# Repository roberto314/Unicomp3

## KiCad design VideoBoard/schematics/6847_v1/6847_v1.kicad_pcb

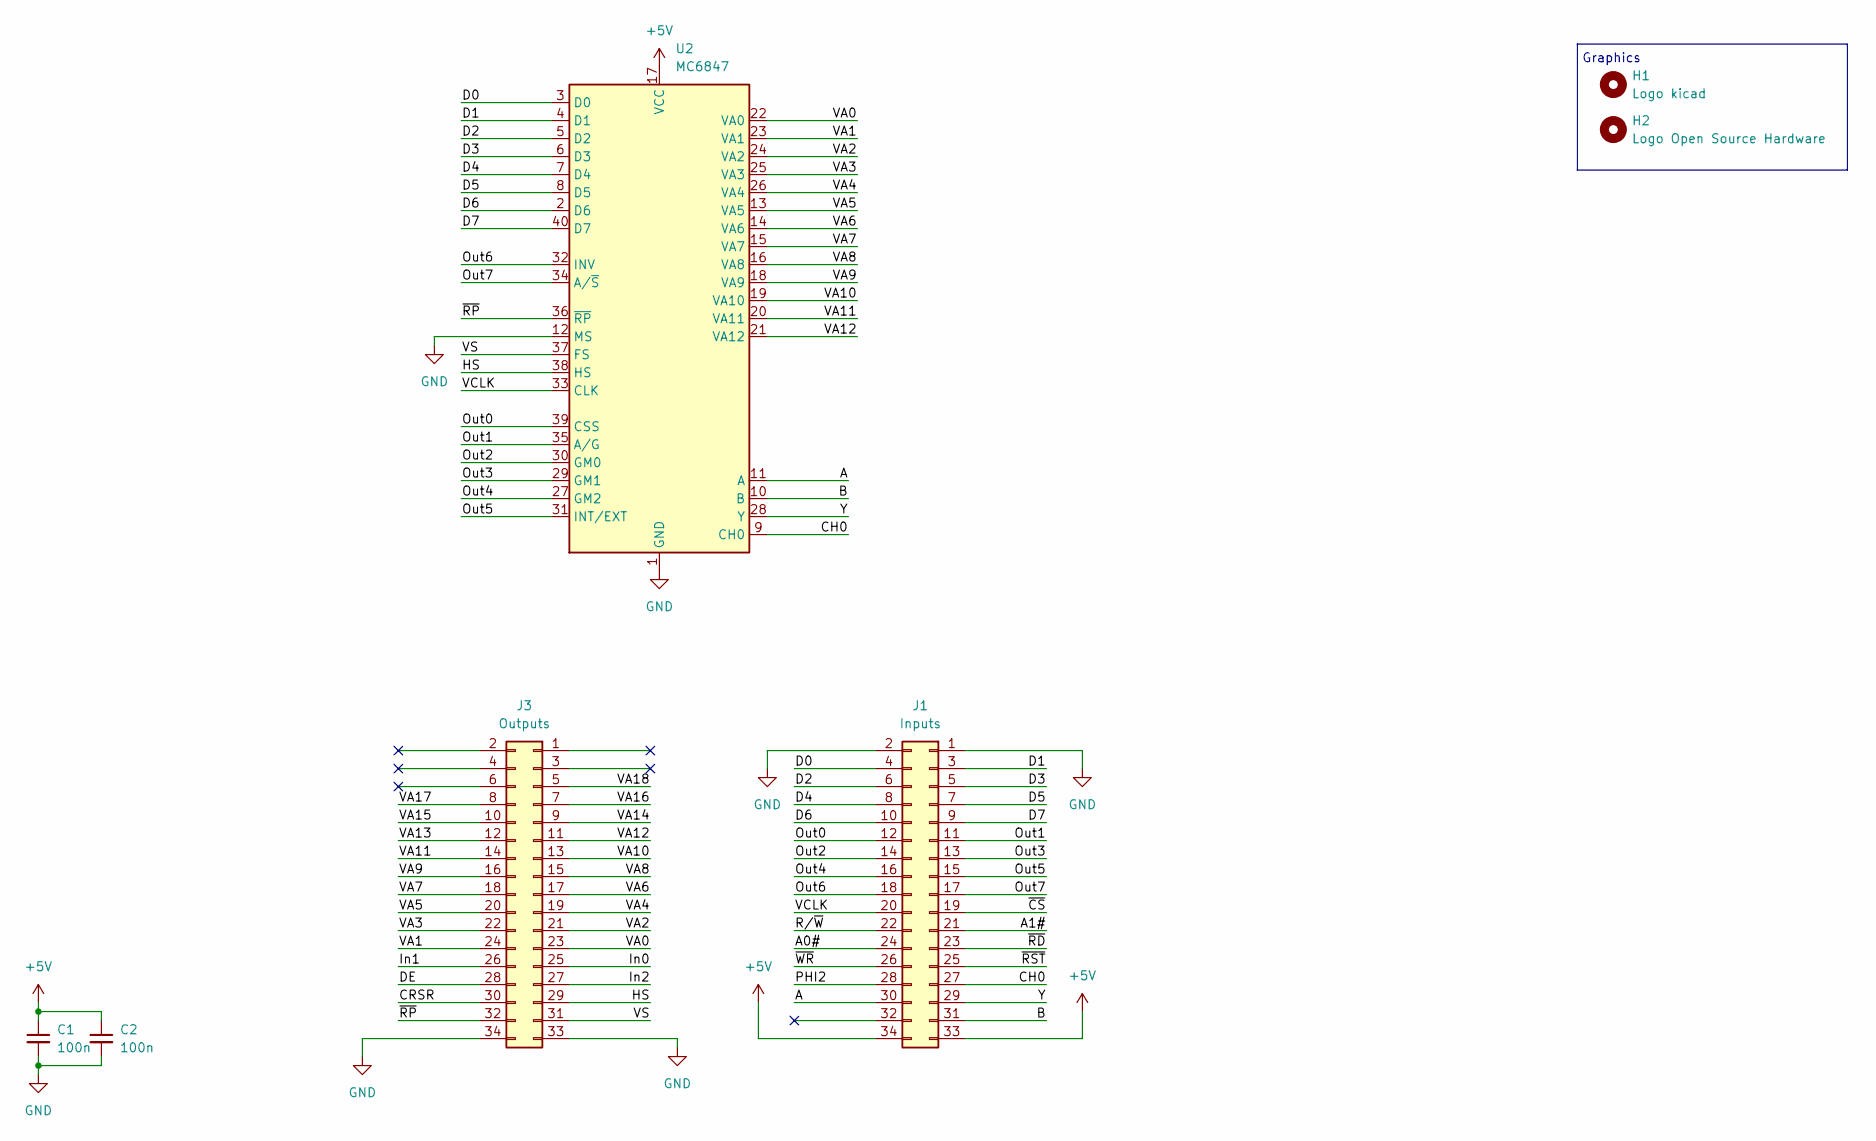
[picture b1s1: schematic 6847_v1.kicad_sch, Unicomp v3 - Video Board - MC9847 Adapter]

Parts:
C1, C2: 100n; C_1206_3216Metric_Pad1.33x1.80mm_HandSolder
H1: Logo kicad; KiCad-Logo2_6mm_SilkScreen
H2: Logo Open Source Hardware; OSHW-Logo2_7.3x6mm_SilkScreen
J1: Inputs; PinHeader_2x17_P2.54mm_Vertical
J3: Outputs; PinHeader_2x17_P2.54mm_Vertical
U2: MC6847; DIP-40_W15.24mm

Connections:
+5V: C1.1, C2.1, J1.33, J1.34, U2.17 (VCC)
/A: J1.30, U2.11 (A)
/A0#: J1.24
/A1#: J1.21
/B: J1.31, U2.10 (B)
/CH0: J1.27, U2.9 (CH0)
/CRSR: J3.30
/D0: J1.4, U2.3 (D0)
/D1: J1.3, U2.4 (D1)
/D2: J1.6, U2.5 (D2)
/D3: J1.5, U2.6 (D3)
/D4: J1.8, U2.7 (D4)
/D5: J1.7, U2.8 (D5)
/D6: J1.10, U2.2 (D6)
/D7: J1.9, U2.40 (D7)
/DE: J3.28
/HS: J3.29, U2.38 (HS)
/In0: J3.25
/In1: J3.26
/In2: J3.27
/Out0: J1.12, U2.39 (CSS)
/Out1: J1.11, U2.35 (A/G)
/Out2: J1.14, U2.30 (GM0)
/Out3: J1.13, U2.29 (GM1)
/Out4: J1.16, U2.27 (GM2)
/Out5: J1.15, U2.31 (INT/EXT)
/Out6: J1.18, U2.32 (INV)
/Out7: J1.17, U2.34 (A/~S)
/PHI2: J1.28
/R/~W: J1.22
/VA0: J3.23, U2.22 (VA0)
/VA1: J3.24, U2.23 (VA1)
/VA2: J3.21, U2.24 (VA2)
/VA3: J3.22, U2.25 (VA3)
/VA4: J3.19, U2.26 (VA4)
/VA5: J3.20, U2.13 (VA5)
/VA6: J3.17, U2.14 (VA6)
/VA7: J3.18, U2.15 (VA7)
/VA8: J3.15, U2.16 (VA8)
/VA9: J3.16, U2.18 (VA9)
/VA10: J3.13, U2.19 (VA10)
/VA11: J3.14, U2.20 (VA11)
/VA12: J3.11, U2.21 (VA12)
/VA13: J3.12
/VA14: J3.9
/VA15: J3.10
/VA16: J3.7
/VA17: J3.8
/VA18: J3.5
/VCLK: J1.20, U2.33 (CLK)
/VS: J3.31, U2.37 (FS)
/Y: J1.29, U2.28 (Y)
/~CS: J1.19
/~RD: J1.23
/~RP: J3.32, U2.36 (~RP)
/~RST: J1.25
/~WR: J1.26
GND: C1.2, C2.2, J1.1, J1.2, J3.33, J3.34, U2.1 (GND), U2.12 (MS)

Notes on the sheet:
Graphics

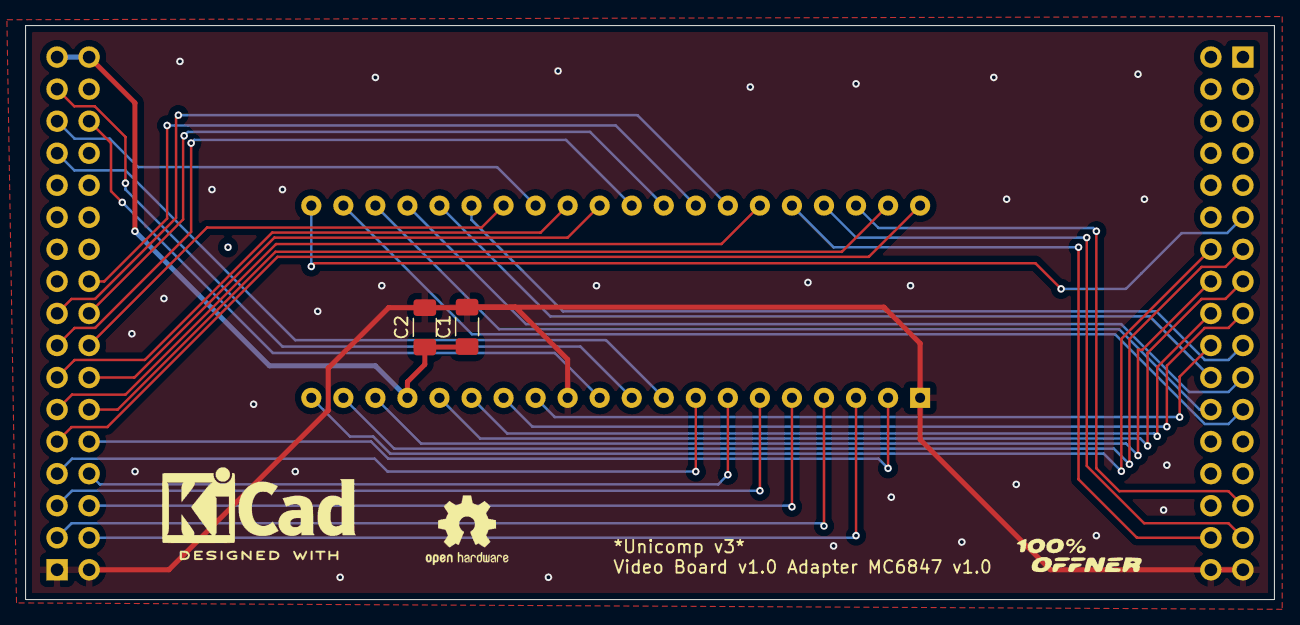
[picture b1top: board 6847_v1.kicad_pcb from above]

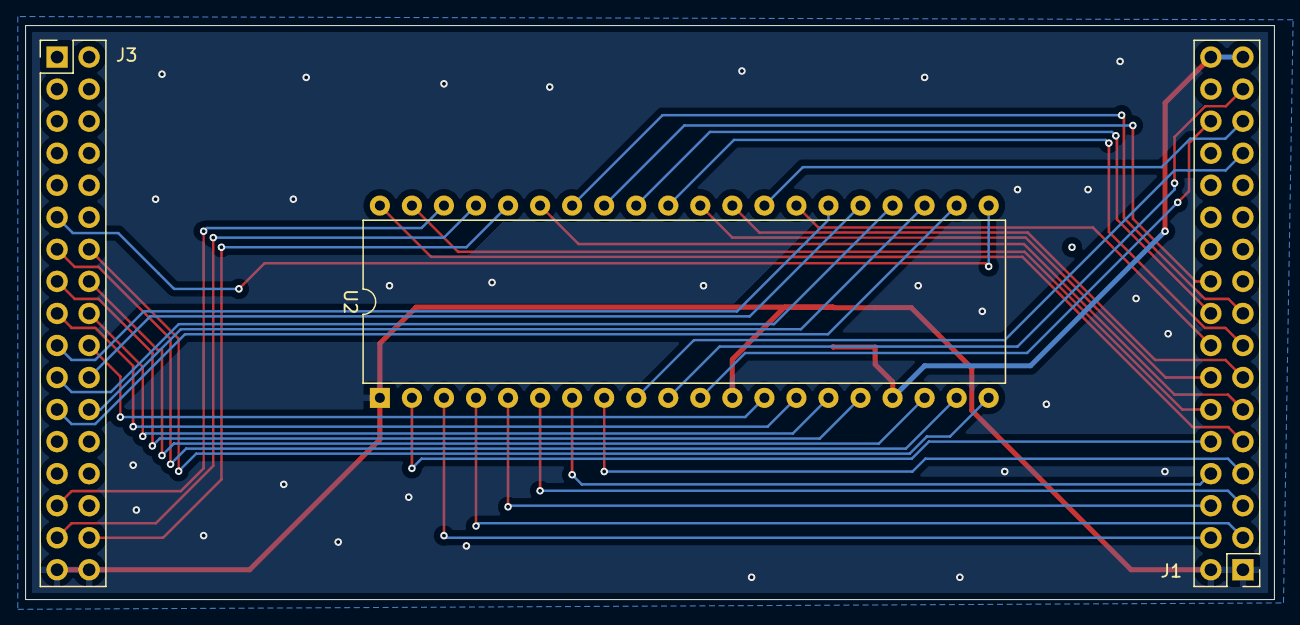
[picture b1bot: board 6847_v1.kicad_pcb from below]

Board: 2 copper layers, 99.0 x 45.5 mm, 7 parts (3 on the bottom side), 39 nets.

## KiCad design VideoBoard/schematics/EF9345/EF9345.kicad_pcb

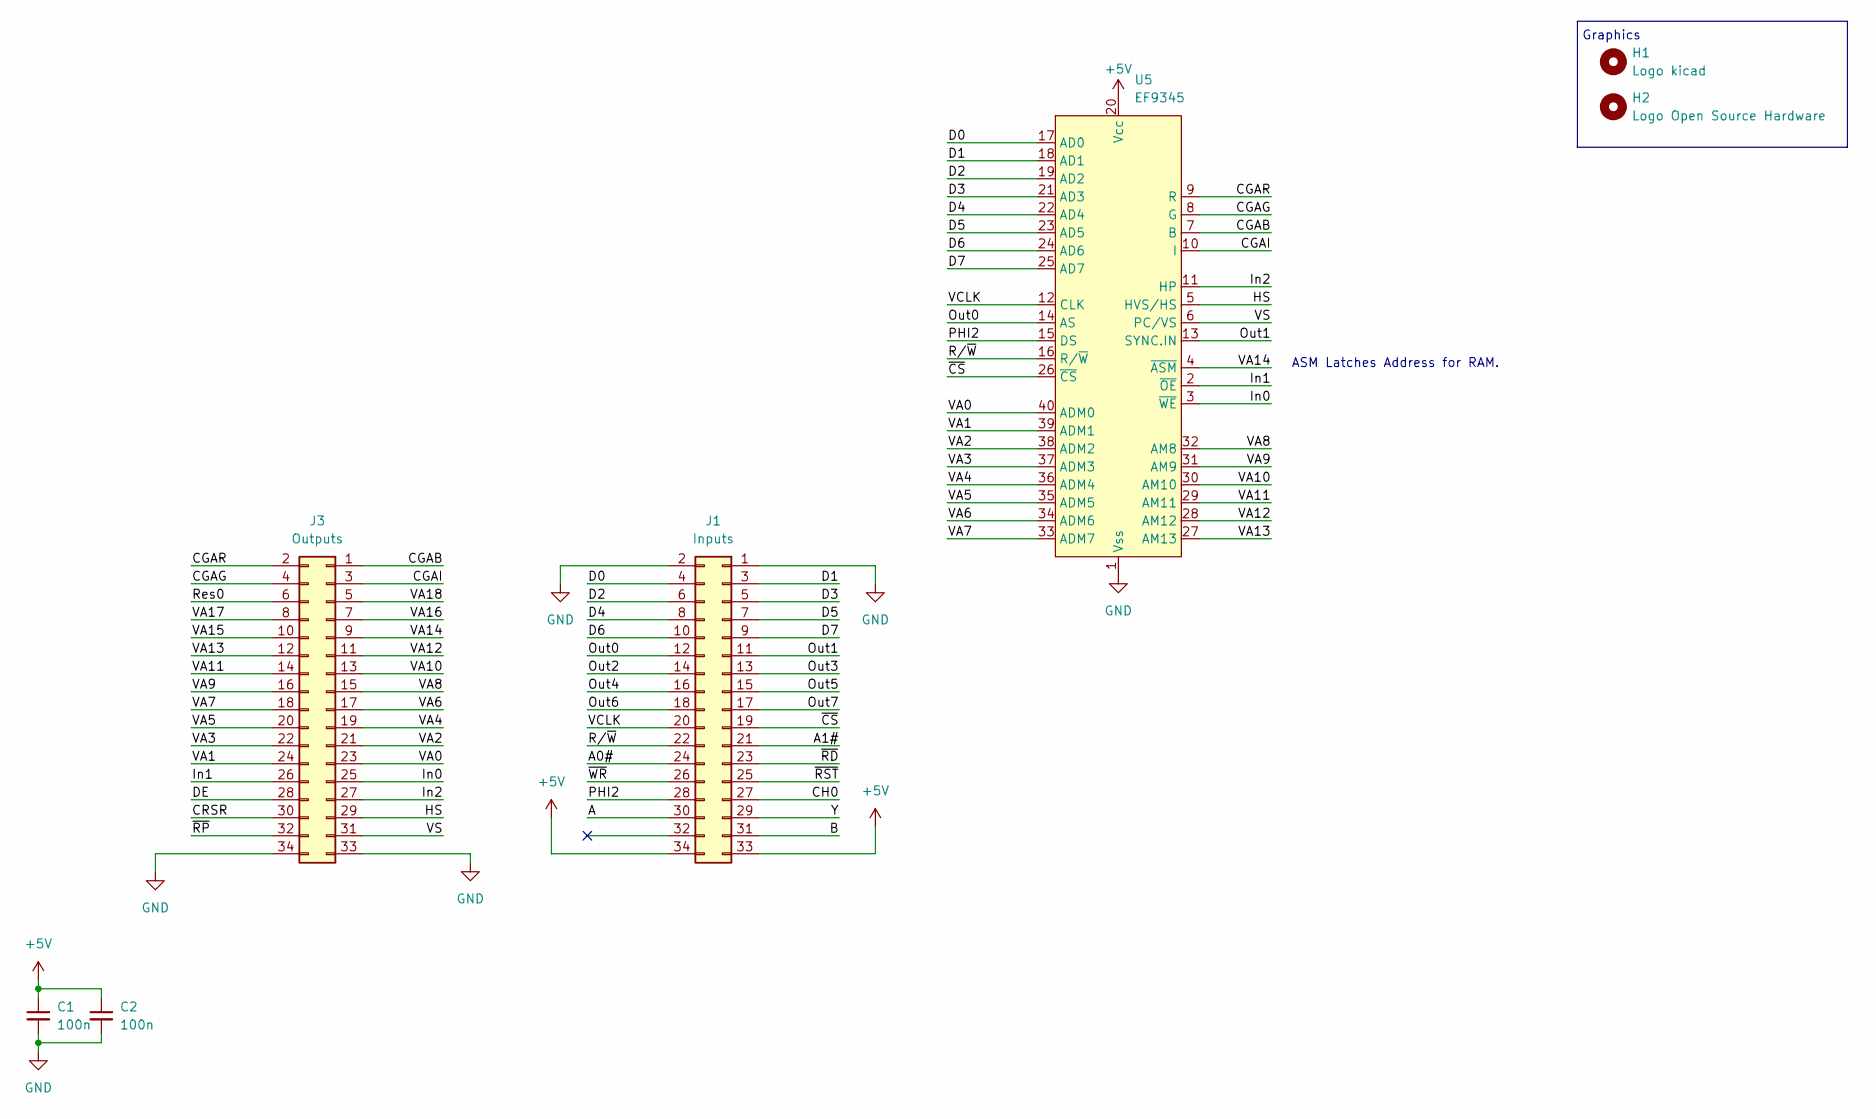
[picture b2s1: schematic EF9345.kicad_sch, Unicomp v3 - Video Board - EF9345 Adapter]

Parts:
C1, C2: 100n; C_1206_3216Metric_Pad1.33x1.80mm_HandSolder
H1: Logo kicad; KiCad-Logo2_6mm_SilkScreen
H2: Logo Open Source Hardware; OSHW-Logo2_7.3x6mm_SilkScreen
J1: Inputs; PinHeader_2x17_P2.54mm_Vertical
J3: Outputs; PinHeader_2x17_P2.54mm_Vertical
U5: EF9345; DIP-40_W15.24mm_Socket

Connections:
+5V: C1.1, C2.1, J1.33, J1.34, U5.20 (Vcc)
/A: J1.30
/A0#: J1.24
/A1#: J1.21
/B: J1.31
/CGAB: J3.1, U5.7 (B)
/CGAG: J3.4, U5.8 (G)
/CGAI: J3.3, U5.10 (I)
/CGAR: J3.2, U5.9 (R)
/CH0: J1.27
/CRSR: J3.30
/D0: J1.4, U5.17 (AD0)
/D1: J1.3, U5.18 (AD1)
/D2: J1.6, U5.19 (AD2)
/D3: J1.5, U5.21 (AD3)
/D4: J1.8, U5.22 (AD4)
/D5: J1.7, U5.23 (AD5)
/D6: J1.10, U5.24 (AD6)
/D7: J1.9, U5.25 (AD7)
/DE: J3.28
/HS: J3.29, U5.5 (HVS/HS)
/In0: J3.25, U5.3 (~WE)
/In1: J3.26, U5.2 (~OE)
/In2: J3.27, U5.11 (HP)
/Out0: J1.12, U5.14 (AS)
/Out1: J1.11, U5.13 (SYNC.IN)
/Out2: J1.14
/Out3: J1.13
/Out4: J1.16
/Out5: J1.15
/Out6: J1.18
/Out7: J1.17
/PHI2: J1.28, U5.15 (DS)
/Res0: J3.6
/R/~W: J1.22, U5.16 (R/~W)
/VA0: J3.23, U5.40 (ADM0)
/VA1: J3.24, U5.39 (ADM1)
/VA2: J3.21, U5.38 (ADM2)
/VA3: J3.22, U5.37 (ADM3)
/VA4: J3.19, U5.36 (ADM4)
/VA5: J3.20, U5.35 (ADM5)
/VA6: J3.17, U5.34 (ADM6)
/VA7: J3.18, U5.33 (ADM7)
/VA8: J3.15, U5.32 (AM8)
/VA9: J3.16, U5.31 (AM9)
/VA10: J3.13, U5.30 (AM10)
/VA11: J3.14, U5.29 (AM11)
/VA12: J3.11, U5.28 (AM12)
/VA13: J3.12, U5.27 (AM13)
/VA14: J3.9, U5.4 (~ASM)
/VA15: J3.10
/VA16: J3.7
/VA17: J3.8
/VA18: J3.5
/VCLK: J1.20, U5.12 (CLK)
/VS: J3.31, U5.6 (PC/VS)
/Y: J1.29
/~CS: J1.19, U5.26 (~CS)
/~RD: J1.23
/~RP: J3.32
/~RST: J1.25
/~WR: J1.26
GND: C1.2, C2.2, J1.1, J1.2, J3.33, J3.34, U5.1 (Vss)

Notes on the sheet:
Graphics
ASM Latches Address for RAM.

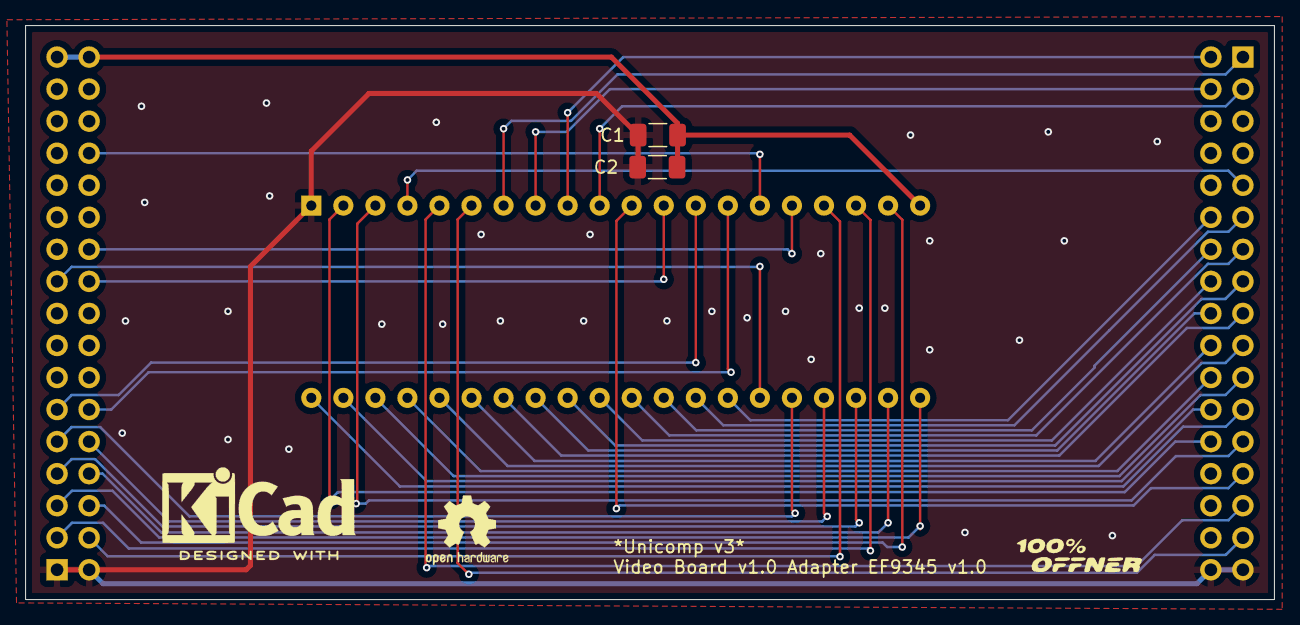
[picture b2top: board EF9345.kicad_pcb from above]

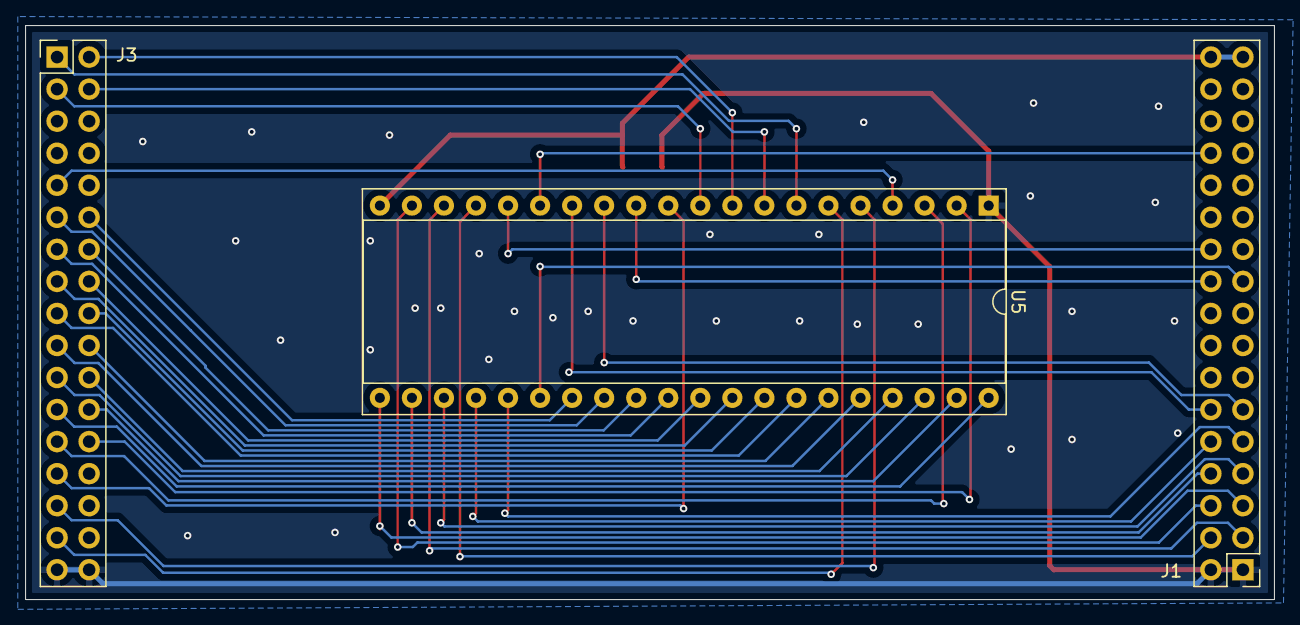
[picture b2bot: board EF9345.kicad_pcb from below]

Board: 2 copper layers, 99.0 x 45.5 mm, 7 parts (3 on the bottom side), 40 nets.

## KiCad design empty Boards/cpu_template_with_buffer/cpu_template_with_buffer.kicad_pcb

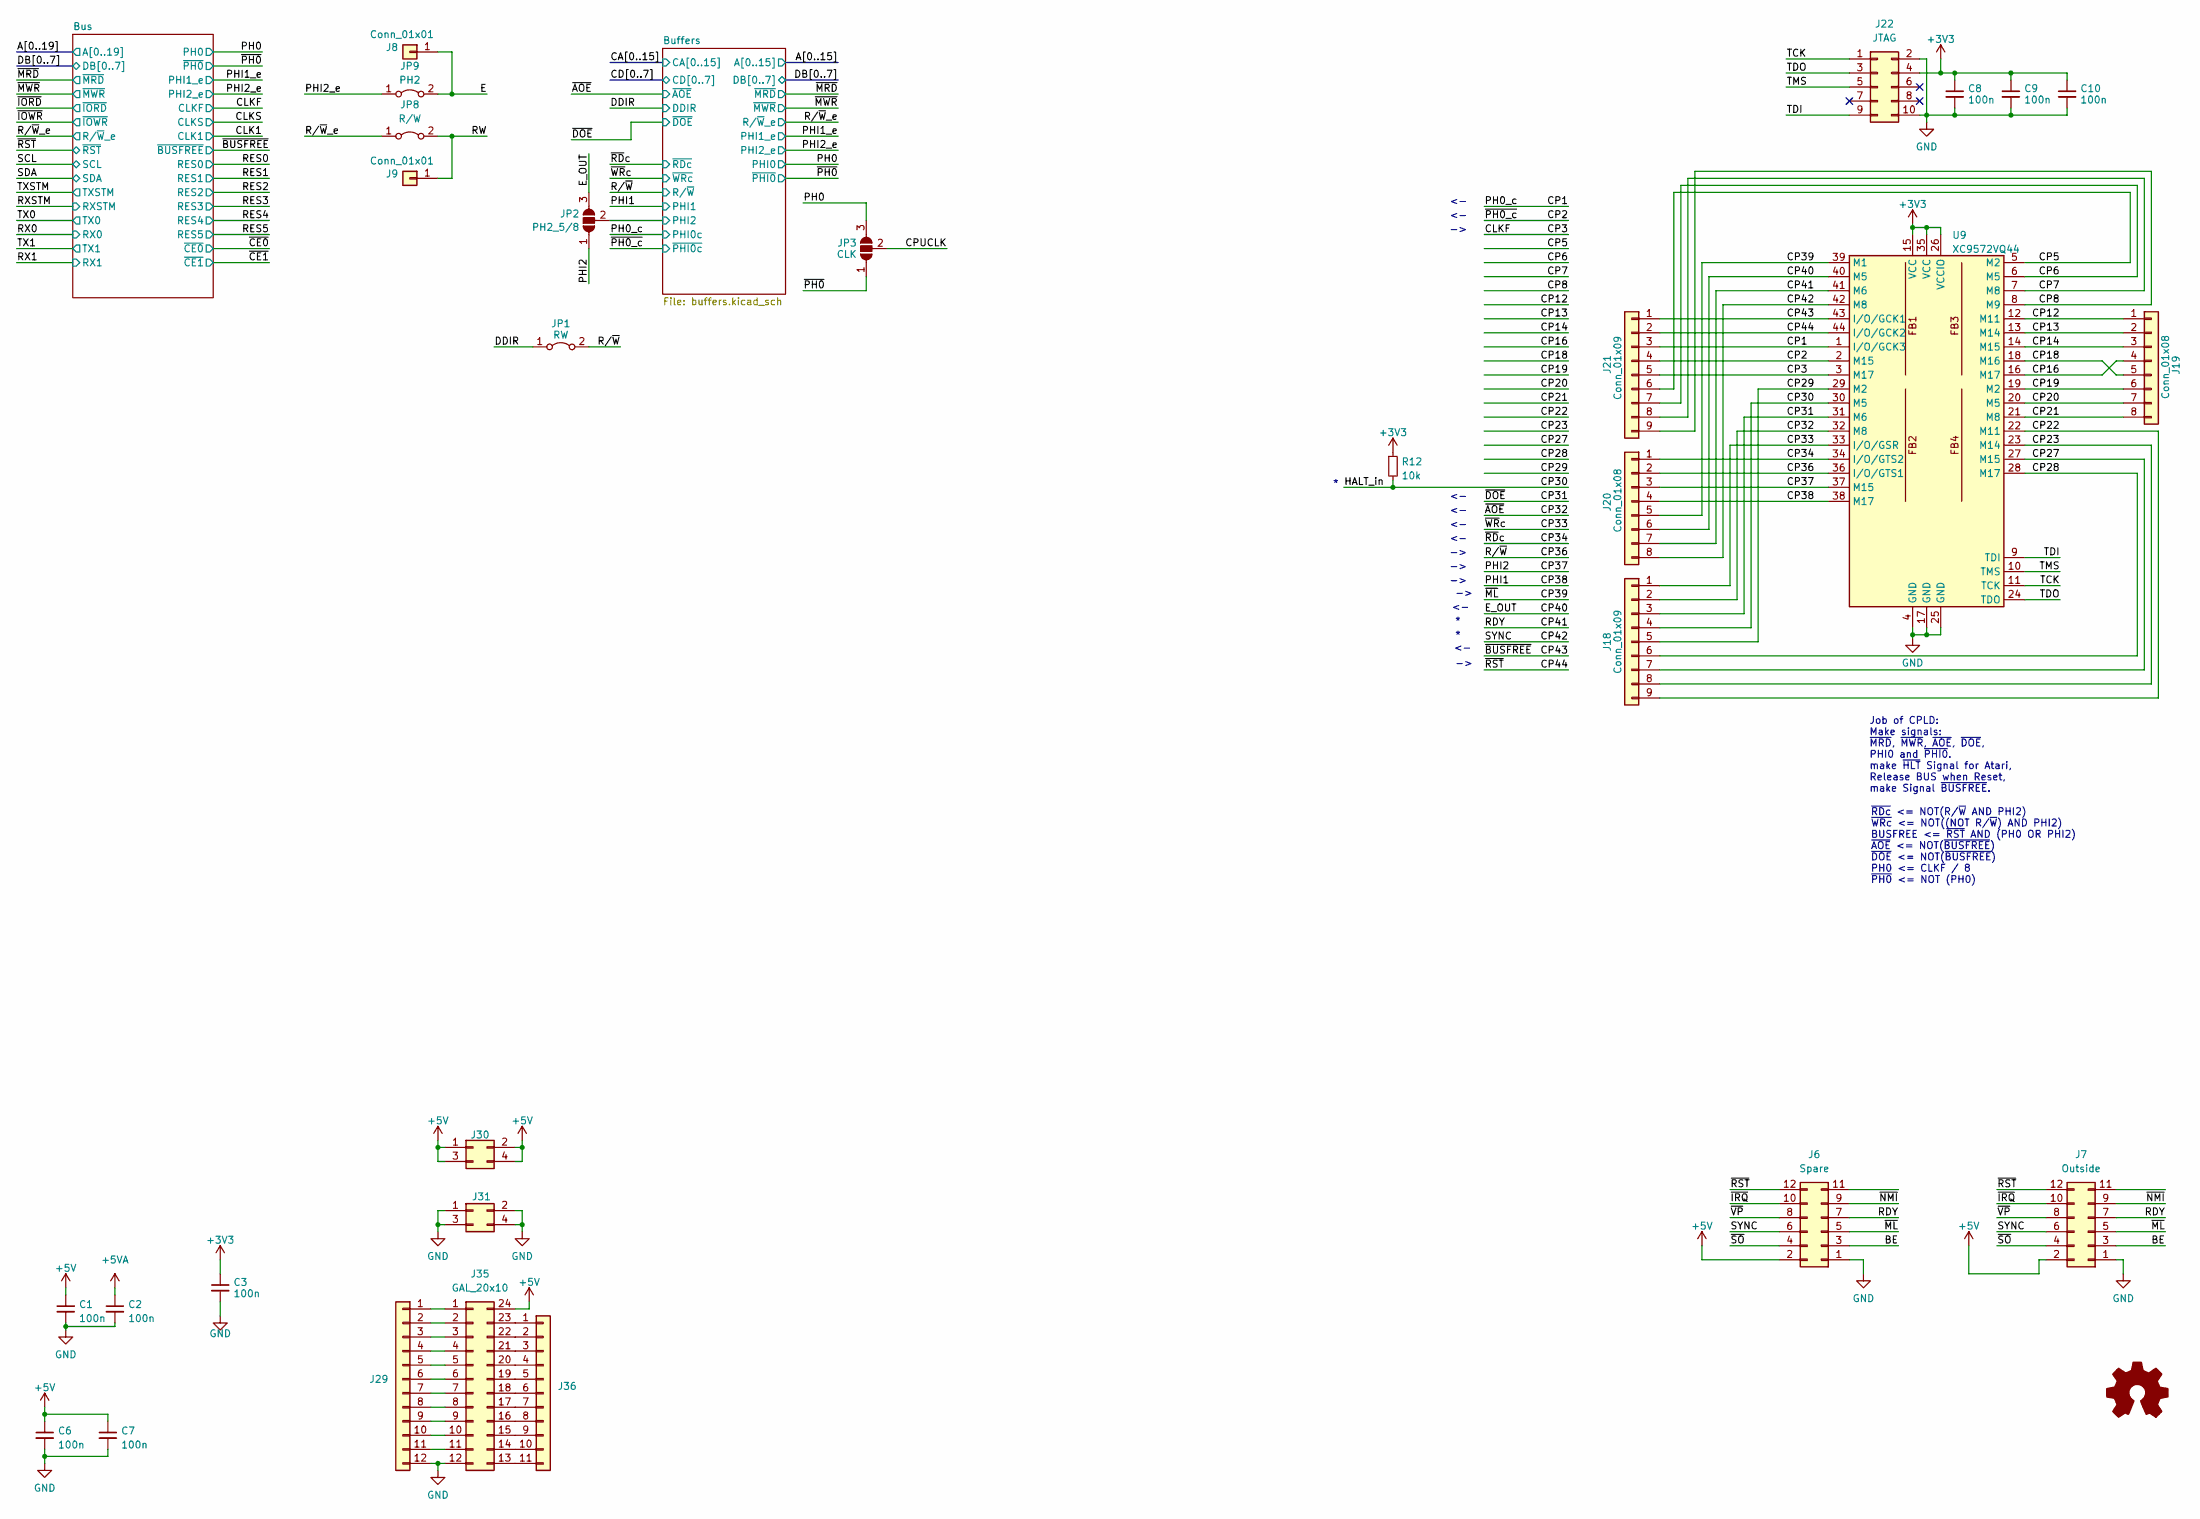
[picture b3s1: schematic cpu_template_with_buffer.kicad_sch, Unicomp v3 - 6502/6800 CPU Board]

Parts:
C1, C2, C3, C6, C7, C8, C9, C10: 100n; C_1206_3216Metric
J6: Spare; PinHeader_2x06_P2.54mm_Vertical
J7: Outside; PinHeader_2x06_P2.54mm_Horizontal
J8, J9: Conn_01x01; PinHeader_1x01_P2.00mm_Vertical
J18, J21: Conn_01x09; PinHeader_1x09_P2.54mm_Vertical
J19, J20: Conn_01x08; PinHeader_1x08_P2.54mm_Vertical
J22: JTAG; PinHeader_2x05_P2.54mm_Horizontal
J29: Conn_01x12; PinSocket_1x12_P2.54mm_Vertical
J30, J31: Conn_02x02_Odd_Even; PinSocket_2x02_P2.54mm_Vertical
J35: GAL_20x10; DIP-24_W7.62mm
J36: Conn_01x11; PinSocket_1x11_P2.54mm_Vertical
JP1: RW; SolderJumper-2_P1.3mm_Bridged_RoundedPad1.0x1.5mm
JP2: PH2_5/8; SolderJumper-3_P1.3mm_Open_RoundedPad1.0x1.5mm_NumberLabels
JP3: CLK; SolderJumper-3_P1.3mm_Open_RoundedPad1.0x1.5mm_NumberLabels
JP8: R/W; SolderJumper-2_P1.3mm_Bridged_RoundedPad1.0x1.5mm
JP9: PH2; SolderJumper-2_P1.3mm_Bridged_RoundedPad1.0x1.5mm
R12: 10k; R_1206_3216Metric_Pad1.30x1.75mm_HandSolder
U9: XC9572VQ44; TQFP-44_10x10mm_P0.8mm

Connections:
+3V3: C3.1, C8.1, C9.1, C10.1, J22.4, R12.1, U9.15 (VCC), U9.26 (VCCIO), U9.35 (VCC); also elsewhere on the board
+5V: C1.1, C6.1, C7.1, J6.2, J7.2, J30.1, J30.2, J30.3, J30.4, J35.24; also elsewhere on the board
+5VA: C2.1; also elsewhere on the board
/BE: J6.3, J7.3
/Buffers/PHI2: JP2.2 (C); also elsewhere on the board
/CLKF: J21.5, U9.3 (M17); also elsewhere on the board
/CP1: J21.3, U9.1 (I/O/GCK3); also elsewhere on the board
/CP2: J21.4, U9.2 (M15); also elsewhere on the board
/CP5: J21.6, U9.5 (M2)
/CP6: J21.7, U9.6 (M5)
/CP7: J21.8, U9.7 (M8)
/CP8: J21.9, U9.8 (M9)
/CP12: J19.1, U9.12 (M11)
/CP13: J19.2, U9.13 (M14)
/CP14: J19.3, U9.14 (M15)
/CP16: J19.4, U9.16 (M17)
/CP18: J19.5, U9.18 (M16)
/CP19: J19.6, U9.19 (M2)
/CP20: J19.7, U9.20 (M5)
/CP21: J19.8, U9.21 (M8)
/CP22: J18.9, U9.22 (M11)
/CP23: J18.8, U9.23 (M14)
/CP27: J18.7, U9.27 (M15)
/CP28: J18.6, U9.28 (M17)
/CP29: J18.5, U9.29 (M2)
/CP30: J18.4, R12.2, U9.30 (M5)
/CP31: J18.3, U9.31 (M6); also elsewhere on the board
/CP32: J18.2, U9.32 (M8); also elsewhere on the board
/CP33: J18.1, U9.33 (I/O/GSR); also elsewhere on the board
/CP34: J20.1, U9.34 (I/O/GTS2); also elsewhere on the board
/CP36: J20.2, JP1.2 (B), U9.36 (I/O/GTS1); also elsewhere on the board
/CP37: J20.3, JP2.1 (A), U9.37 (M15)
/CP38: J20.4, U9.38 (M17); also elsewhere on the board
/CP39: J6.5, J7.5, J20.5, U9.39 (M1)
/CP40: J20.6, JP2.3 (B), U9.40 (M5)
/CP41: J6.7, J7.7, J20.7, U9.41 (M6)
/CP42: J6.6, J7.6, J20.8, U9.42 (M8)
/CP43: J21.1, U9.43 (I/O/GCK1); also elsewhere on the board
/CP44: J6.12, J7.12, J21.2, U9.44 (I/O/GCK2); also elsewhere on the board
/CPUCLK: JP3.2 (C)
/DDIR: JP1.1 (A); also elsewhere on the board
/E: J8.1, JP9.2 (B)
/PH0: JP3.3 (B); also elsewhere on the board
/PHI2_e: JP9.1 (A); also elsewhere on the board
/RW: J9.1, JP8.2 (B)
/R/~W_e: JP8.1 (A); also elsewhere on the board
/TCK: J22.1, U9.11 (TCK)
/TDI: J22.9, U9.9 (TDI)
/TDO: J22.3, U9.24 (TDO)
/TMS: J22.5, U9.10 (TMS)
/~IRQ: J6.10, J7.10
/~NMI: J6.9, J7.9
/~PH0: JP3.1 (A); also elsewhere on the board
/~SO: J6.4, J7.4
/~VP: J6.8, J7.8
GND: C1.2, C2.2, C3.2, C6.2, C7.2, C8.2, C9.2, C10.2, J6.1, J7.1, J22.2, J22.10, J29.12, J31.1, J31.2, J31.3, J31.4, J35.12, U9.4 (GND), U9.17 (GND), U9.25 (GND); also elsewhere on the board
unnamed: J29.1, J35.1
unnamed: J29.2, J35.2
unnamed: J29.3, J35.3
unnamed: J29.4, J35.4
unnamed: J29.5, J35.5
unnamed: J29.6, J35.6
unnamed: J29.7, J35.7
unnamed: J29.8, J35.8
unnamed: J29.9, J35.9
unnamed: J29.10, J35.10
unnamed: J29.11, J35.11
unnamed: J35.13, J36.11
unnamed: J35.14, J36.10
unnamed: J35.15, J36.9
unnamed: J35.16, J36.8
unnamed: J35.17, J36.7
unnamed: J35.18, J36.6
unnamed: J35.19, J36.5
unnamed: J35.20, J36.4
unnamed: J35.21, J36.3
unnamed: J35.22, J36.2
unnamed: J35.23, J36.1

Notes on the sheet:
Job of CPLD: Make signals: ~{MRD}, ~{MWR}, ~{AOE}, ~{DOE}, PHI0 and ~{PHI0}. make ~{HLT} Signal for Atari, Release BUS when Reset, make Signal ~{BUSFREE}.
~{RDc} <= NOT(R/~{W} AND PHI2) ~{WRc} <= NOT((NOT R/~{W}) AND PHI2) BUSFREE <= ~{RST} AND (PH0 OR PHI2) ~{AOE} <= NOT(~{BUSFREE}) ~{DOE} <= NOT(~{BUSFREE}) PH0 <= CLKF / 8 ~{PH0} <= NOT (PH0)

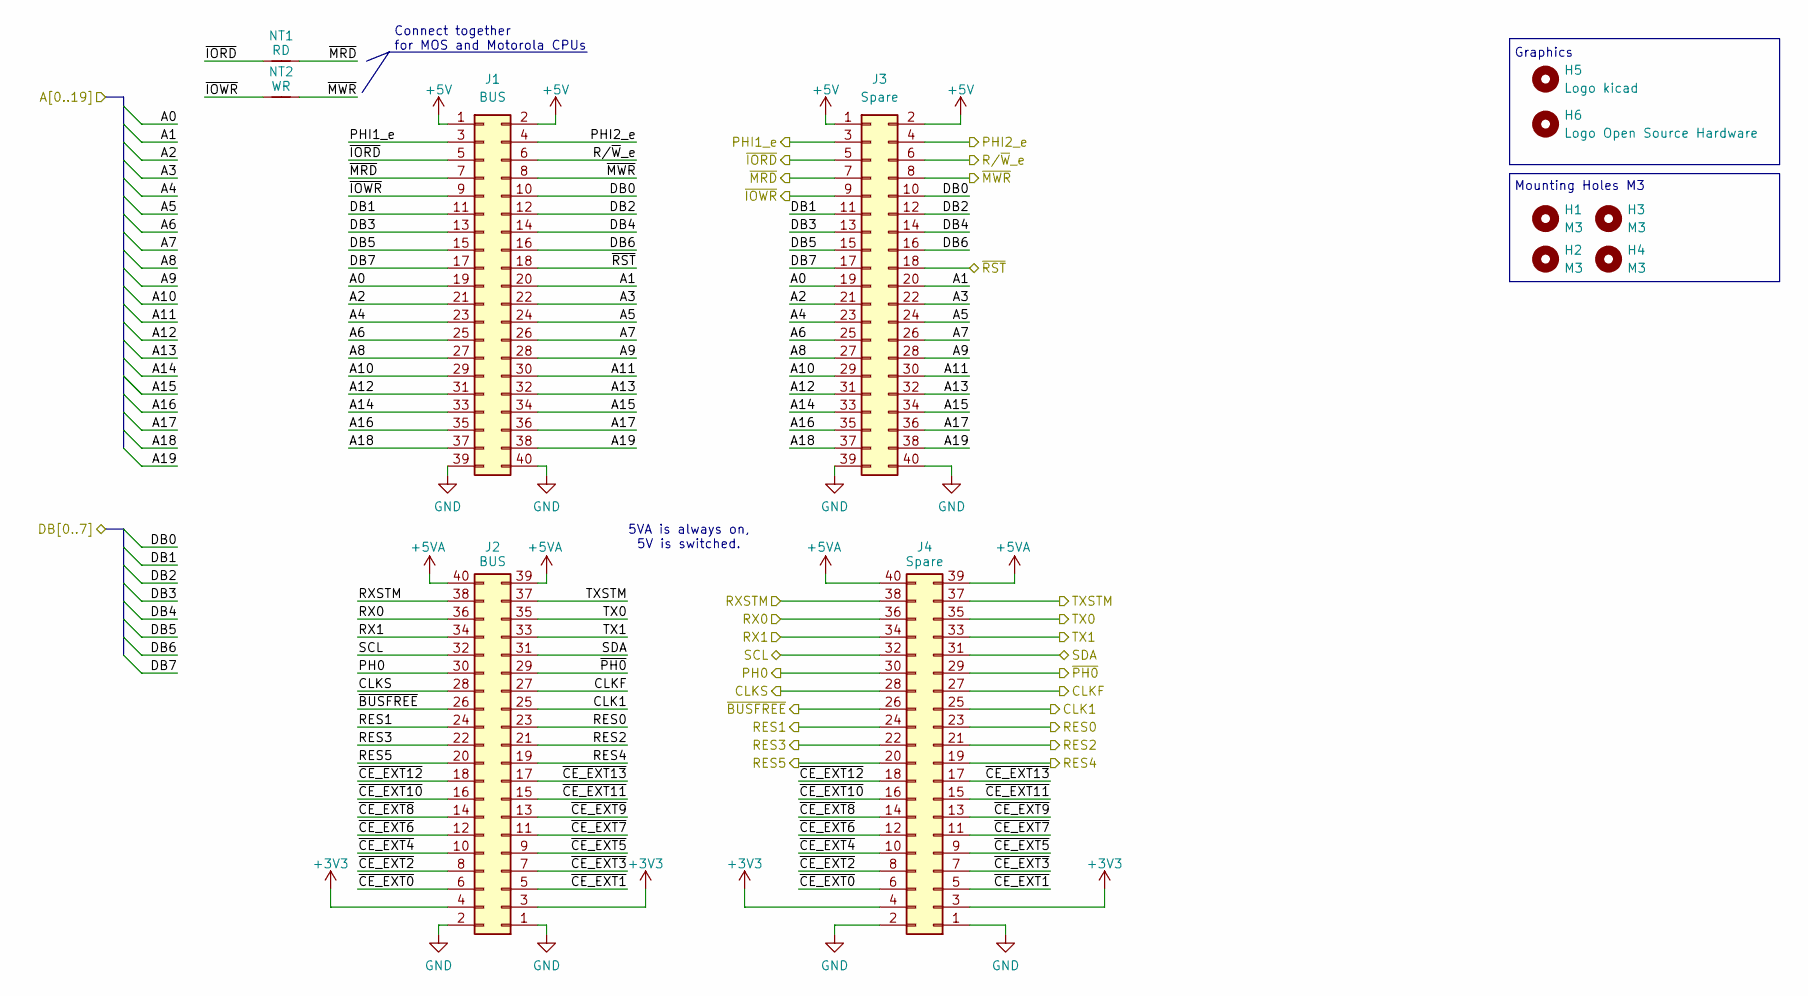
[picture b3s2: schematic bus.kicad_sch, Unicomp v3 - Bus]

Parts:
H1, H2, H3, H4: M3; MountingHole_3.2mm_M3
H5: Logo kicad; KiCad-Logo2_6mm_SilkScreen
H6: Logo Open Source Hardware; OSHW-Logo2_7.3x6mm_SilkScreen
J1, J2: BUS; PinSocket_2x20_P2.54mm_Vertical
J3, J4: Spare; PinSocket_2x20_P2.54mm_Vertical
NT1: RD; NetTie-2_SMD_Pad0.5mm
NT2: WR; NetTie-2_SMD_Pad0.5mm

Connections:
+3V3: J2.3, J2.4, J4.3, J4.4; also elsewhere on the board
+5V: J1.1, J1.2, J3.1, J3.2; also elsewhere on the board
+5VA: J2.39, J2.40, J4.39, J4.40; also elsewhere on the board
/A0: J1.19, J3.19; also elsewhere on the board
/A1: J1.20, J3.20; also elsewhere on the board
/A2: J1.21, J3.21; also elsewhere on the board
/A3: J1.22, J3.22; also elsewhere on the board
/A4: J1.23, J3.23; also elsewhere on the board
/A5: J1.24, J3.24; also elsewhere on the board
/A6: J1.25, J3.25; also elsewhere on the board
/A7: J1.26, J3.26; also elsewhere on the board
/A8: J1.27, J3.27; also elsewhere on the board
/A9: J1.28, J3.28; also elsewhere on the board
/A10: J1.29, J3.29; also elsewhere on the board
/A11: J1.30, J3.30; also elsewhere on the board
/A12: J1.31, J3.31; also elsewhere on the board
/A13: J1.32, J3.32; also elsewhere on the board
/A14: J1.33, J3.33; also elsewhere on the board
/A15: J1.34, J3.34; also elsewhere on the board
/A16: J1.35, J3.35
/A17: J1.36, J3.36
/A18: J1.37, J3.37
/A19: J1.38, J3.38
/Bus/~CE_EXT0: J2.6, J4.6
/Bus/~CE_EXT1: J2.5, J4.5
/Bus/~CE_EXT2: J2.8, J4.8
/Bus/~CE_EXT3: J2.7, J4.7
/Bus/~CE_EXT4: J2.10, J4.10
/Bus/~CE_EXT5: J2.9, J4.9
/Bus/~CE_EXT6: J2.12, J4.12
/Bus/~CE_EXT7: J2.11, J4.11
/Bus/~CE_EXT8: J2.14, J4.14
/Bus/~CE_EXT9: J2.13, J4.13
/Bus/~CE_EXT10: J2.16, J4.16
/Bus/~CE_EXT11: J2.15, J4.15
/Bus/~CE_EXT12: J2.18, J4.18
/Bus/~CE_EXT13: J2.17, J4.17
/CLK1: J2.25, J4.25
/CLKF: J2.27, J4.27; also elsewhere on the board
/CLKS: J2.28, J4.28
/CP43: J2.26, J4.26; also elsewhere on the board
/CP44: J1.18, J3.18; also elsewhere on the board
/DB0: J1.10, J3.10; also elsewhere on the board
/DB1: J1.11, J3.11; also elsewhere on the board
/DB2: J1.12, J3.12; also elsewhere on the board
/DB3: J1.13, J3.13; also elsewhere on the board
/DB4: J1.14, J3.14; also elsewhere on the board
/DB5: J1.15, J3.15; also elsewhere on the board
/DB6: J1.16, J3.16; also elsewhere on the board
/DB7: J1.17, J3.17; also elsewhere on the board
/PH0: J2.30, J4.30; also elsewhere on the board
/PHI1_e: J1.3, J3.3; also elsewhere on the board
/PHI2_e: J1.4, J3.4; also elsewhere on the board
/RES0: J2.23, J4.23
/RES1: J2.24, J4.24
/RES2: J2.21, J4.21
/RES3: J2.22, J4.22
/RES4: J2.19, J4.19
/RES5: J2.20, J4.20
/RX0: J2.36, J4.36
/RX1: J2.34, J4.34
/RXSTM: J2.38, J4.38
/R/~W_e: J1.6, J3.6; also elsewhere on the board
/SCL: J2.32, J4.32
/SDA: J2.31, J4.31
/TX0: J2.35, J4.35
/TX1: J2.33, J4.33
/TXSTM: J2.37, J4.37
/~IORD: J1.5, J3.5, NT1.1
/~IOWR: J1.9, J3.9, NT2.1
/~MRD: J1.7, J3.7, NT1.2; also elsewhere on the board
/~MWR: J1.8, J3.8, NT2.2; also elsewhere on the board
/~PH0: J2.29, J4.29; also elsewhere on the board
GND: J1.39, J1.40, J2.1, J2.2, J3.39, J3.40, J4.1, J4.2; also elsewhere on the board

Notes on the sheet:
Graphics
Connect together for MOS and Motorola CPUs
5VA is always on, 5V is switched.
Mounting Holes M3
